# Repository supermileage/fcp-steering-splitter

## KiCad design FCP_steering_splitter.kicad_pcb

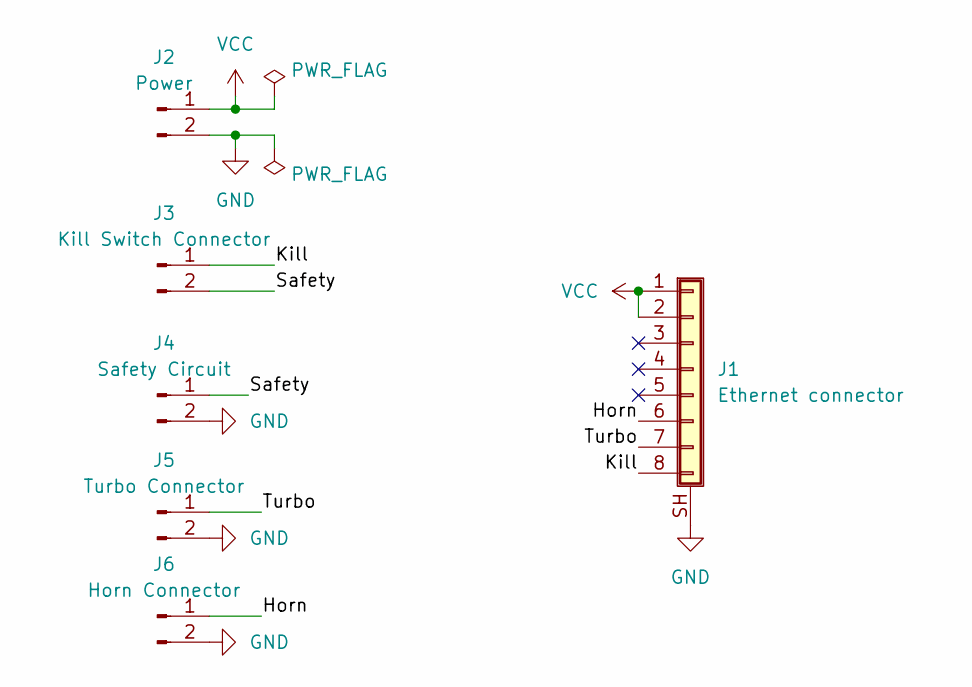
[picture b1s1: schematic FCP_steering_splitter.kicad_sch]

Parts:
J1: Ethernet connector; RJ45_Amphenol_RJHSE5380
J2: Power; Molex_Mini-Fit_Jr_5569-02A2_2x01_P4.20mm_Horizontal
J3: Kill Switch Connector; Molex_Mini-Fit_Jr_5569-02A2_2x01_P4.20mm_Horizontal
J4: Safety Circuit; Molex_Mini-Fit_Jr_5569-02A2_2x01_P4.20mm_Horizontal
J5: Turbo Connector; Molex_Mini-Fit_Jr_5569-02A2_2x01_P4.20mm_Horizontal
J6: Horn Connector; Molex_Mini-Fit_Jr_5569-02A2_2x01_P4.20mm_Horizontal

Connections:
/Horn: J1.6, J6.1
/Kill: J1.8, J3.1
/Safety: J3.2, J4.1
/Turbo: J1.7, J5.1
GND: J1.SH (Shield), J2.2, J4.2, J5.2, J6.2
VCC: J1.1, J1.2, J2.1

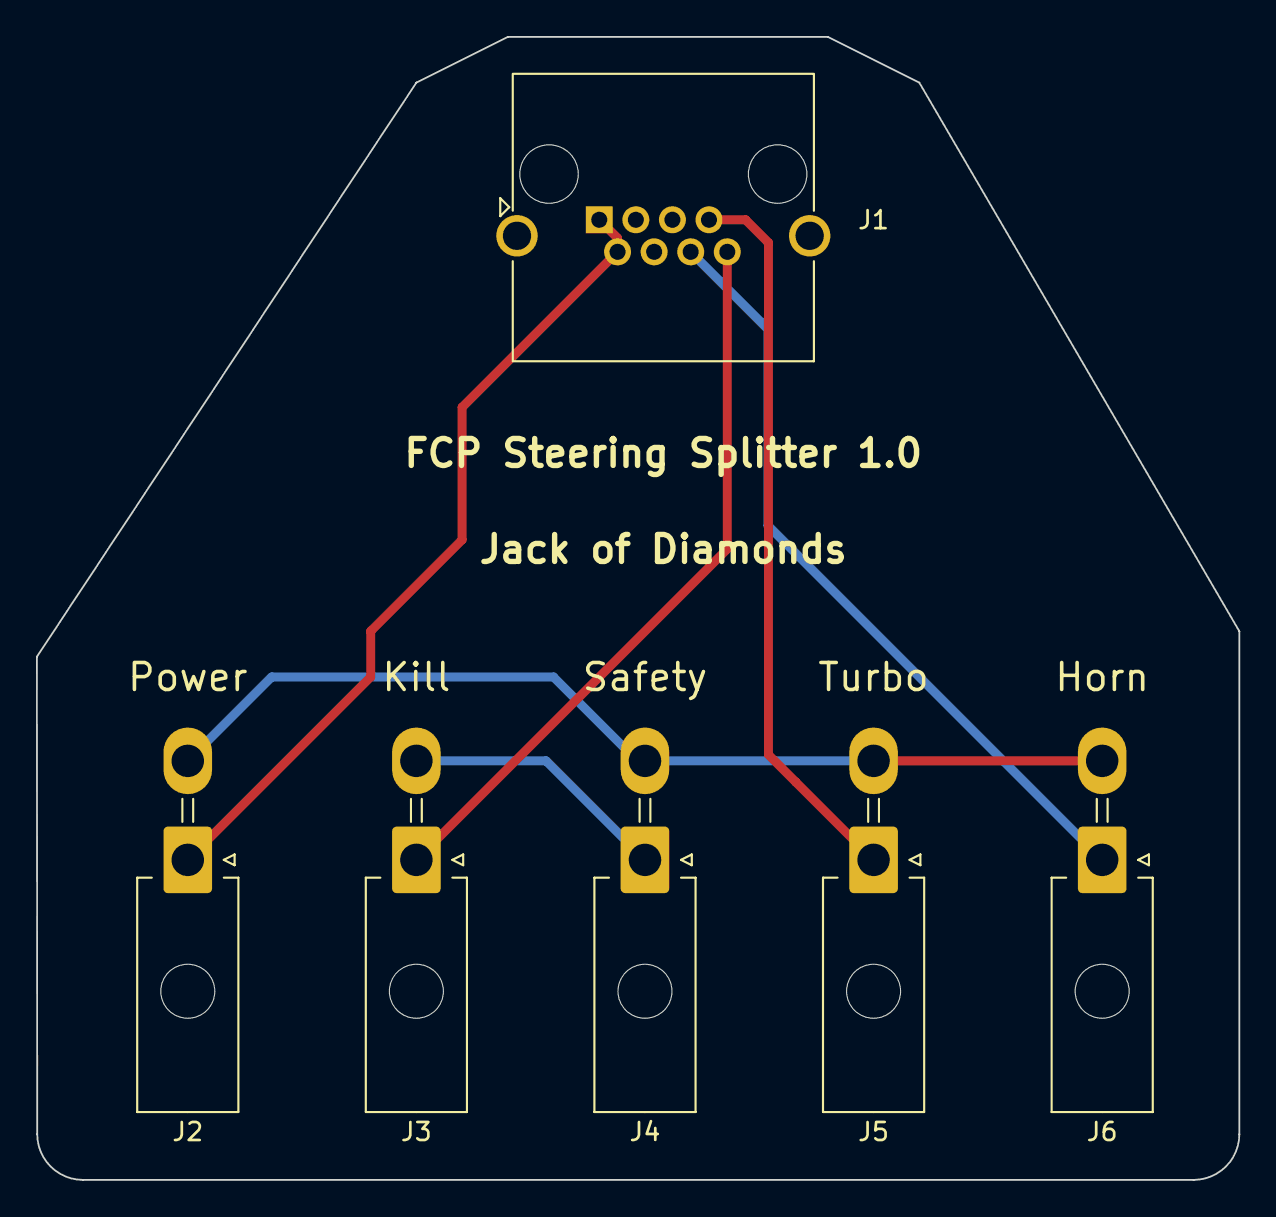
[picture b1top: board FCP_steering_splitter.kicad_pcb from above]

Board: 2 copper layers, 66.8 x 63.5 mm, 6 parts (0 on the bottom side), 6 nets.
